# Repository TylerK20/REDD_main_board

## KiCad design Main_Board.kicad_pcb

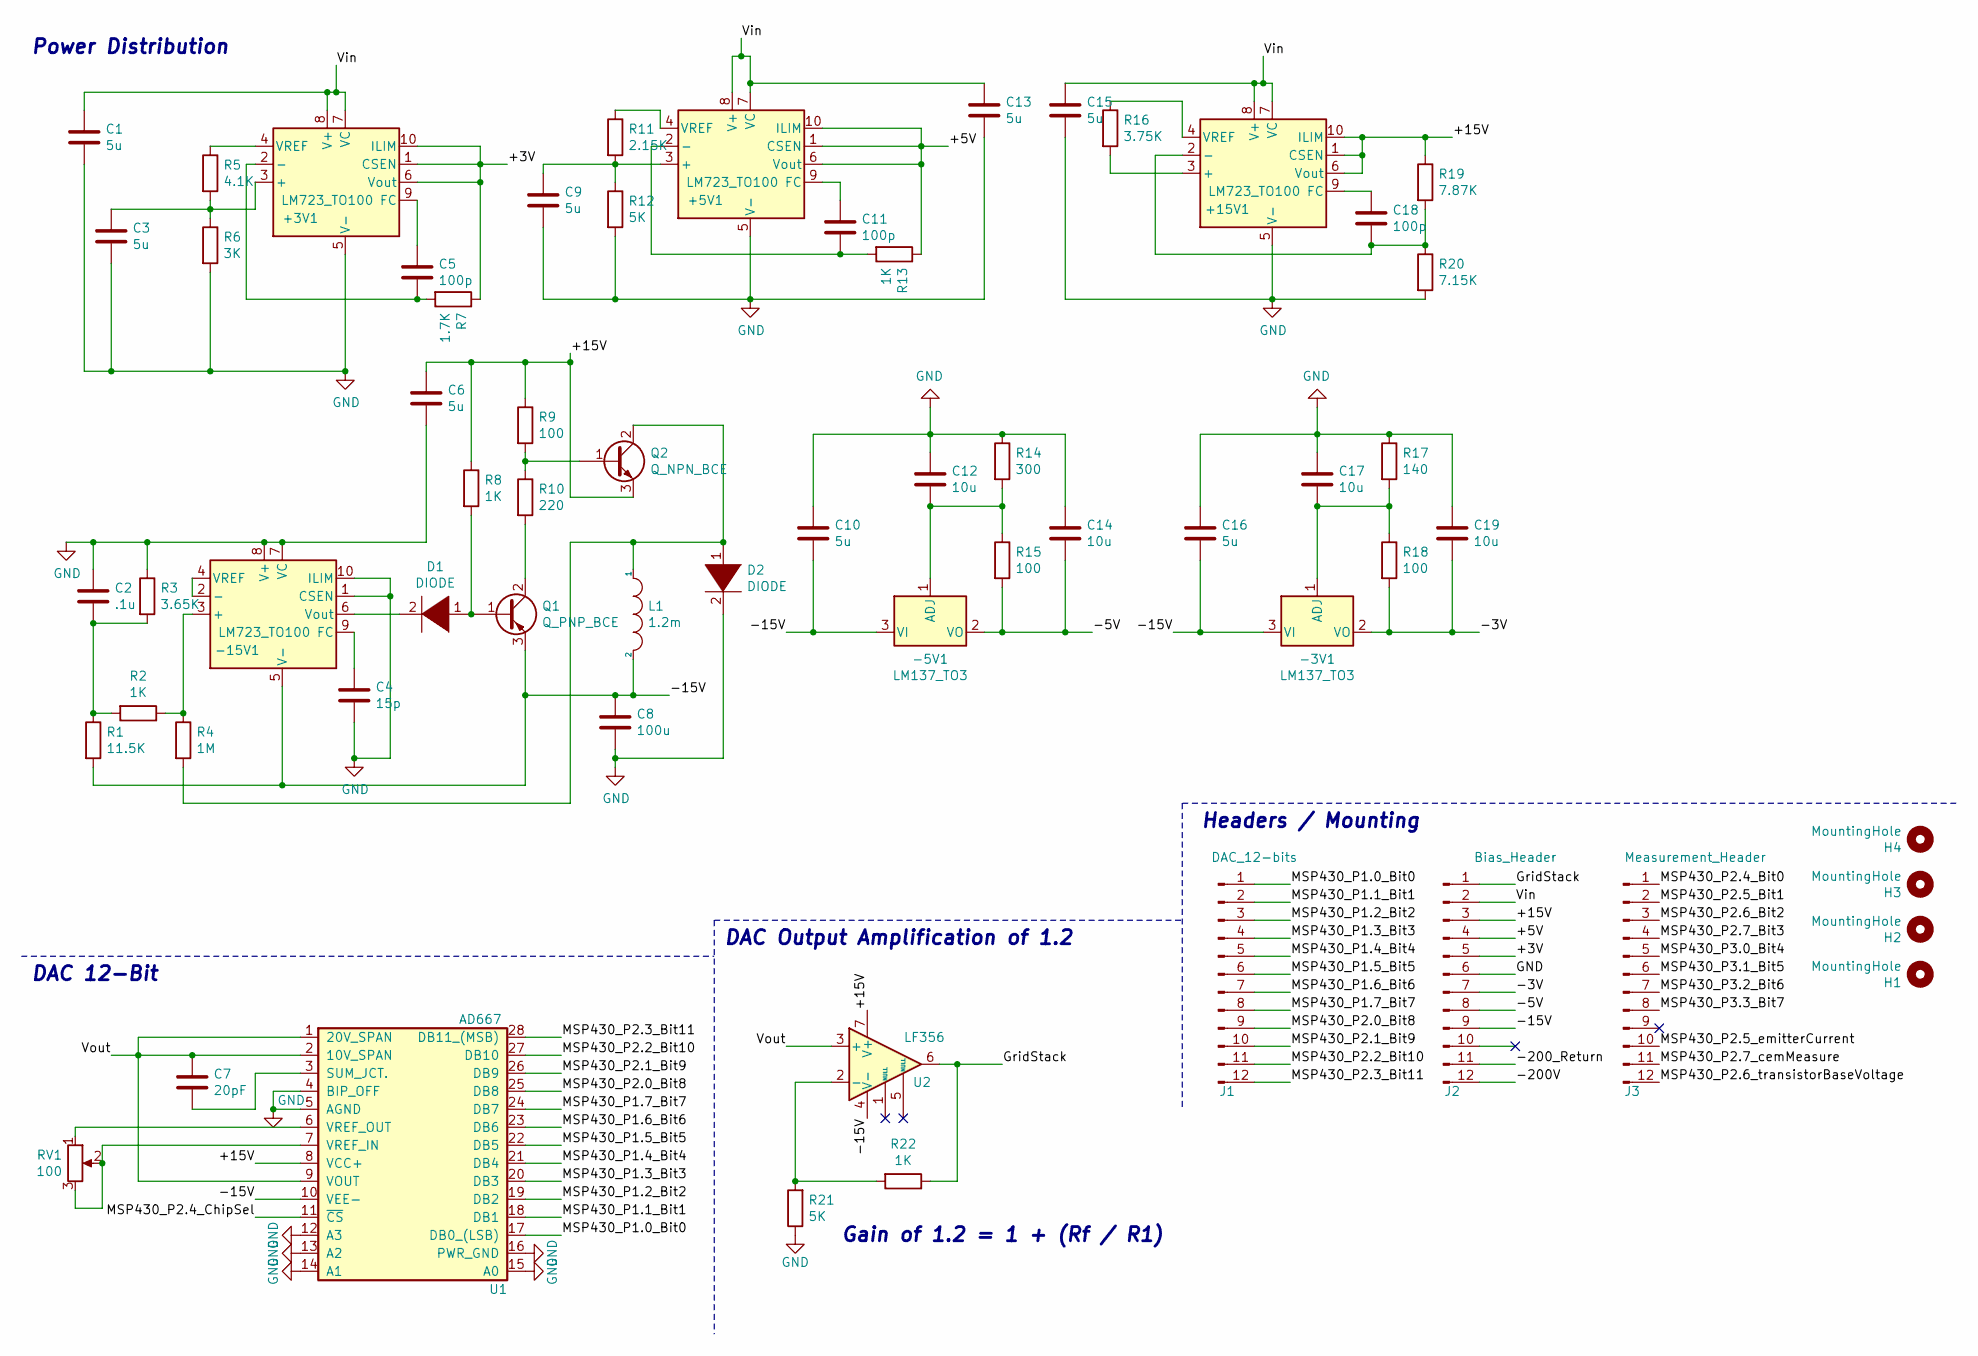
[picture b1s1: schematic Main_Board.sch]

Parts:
+3V1, +5V1, +15V1: LM723_TO100; TO-100-10
-3V1, -5V1: LM137_TO3; TO-39-3
-15V1: LM723_TO100; TO-100-10
C1, C3, C6, C9, C10, C13, C15, C16: 5u; C_0805_2012Metric
C2: .1u; C_0805_2012Metric
C4: 15p; C_0805_2012Metric
C5, C11, C18: 100p; C_0805_2012Metric
C7: 20pF; C_0805_2012Metric
C8: 100u; C_0805_2012Metric
C12, C14, C17, C19: 10u; C_0805_2012Metric
D1: DIODE; D_SMA
D2: DIODE; D_SMC
H1, H2, H3, H4: MountingHole; MountingHole_3.5mm
J1: DAC_12-bits; PinHeader_1x12_P2.54mm_Vertical
J2: Bias_Header; PinHeader_1x12_P2.54mm_Vertical
J3: Measurement_Header; PinHeader_1x12_P2.54mm_Vertical
L1: 1.2m; L_0805_2012Metric
Q1: Q_PNP_BCE; SOT-23
Q2: Q_NPN_BCE; SOT-223
R1: 11.5K; R_0805_2012Metric
R2, R8, R13, R22: 1K; R_0805_2012Metric
R3: 3.65K; R_0805_2012Metric
R4: 1M; R_0805_2012Metric
R5: 4.1K; R_0805_2012Metric
R6: 3K; R_0805_2012Metric
R7: 1.7K; R_0805_2012Metric
R9, R15, R18: 100; R_0805_2012Metric
R10: 220; R_0805_2012Metric
R11: 2.15K; R_0805_2012Metric
R12, R21: 5K; R_0805_2012Metric
R14: 300; R_0805_2012Metric
R16: 3.75K; R_0805_2012Metric
R17: 140; R_0805_2012Metric
R19: 7.87K; R_0805_2012Metric
R20: 7.15K; R_0805_2012Metric
RV1: 100; Potentiometer_Bourns_3299W_Vertical
U1: AD667; AD667_12-bit_DAC
U2: LF356; DIP-8_W7.62mm

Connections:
/+3V: +3V1.1 (CSEN), +3V1.6 (Vout), +3V1.10 (ILIM), J2.5, R7.1
/+5V: +5V1.1 (CSEN), +5V1.6 (Vout), +5V1.10 (ILIM), J2.4, R13.1
/+15V: +15V1.1 (CSEN), +15V1.6 (Vout), +15V1.10 (ILIM), C6.1, J2.3, Q2.3 (E), R8.1, R9.1, R19.1, U1.8 (VCC+), U2.7 (V+)
/-3V: -3V1.2 (VO), C19.2, J2.7, R18.2
/-5V: -5V1.2 (VO), C14.2, J2.8, R15.2
/-15V: -3V1.3 (VI), -5V1.3 (VI), -15V1.5 (V-), C8.1, C10.2, C16.2, J2.9, L1.2, Q1.3 (E), R1.2, U1.10 (VEE-), U2.4 (V-)
/-200V: J2.12
/-200_Return: J2.11
/GridStack: J2.1, R22.1, U2.6
/MSP430_P1.0_Bit0: J1.1, U1.17 (DB0_(LSB))
/MSP430_P1.1_Bit1: J1.2, U1.18 (DB1)
/MSP430_P1.2_Bit2: J1.3, U1.19 (DB2)
/MSP430_P1.3_Bit3: J1.4, U1.20 (DB3)
/MSP430_P1.4_Bit4: J1.5, U1.21 (DB4)
/MSP430_P1.5_Bit5: J1.6, U1.22 (DB5)
/MSP430_P1.6_Bit6: J1.7, U1.23 (DB6)
/MSP430_P1.7_Bit7: J1.8, U1.24 (DB7)
/MSP430_P2.0_Bit8: J1.9, U1.25 (DB8)
/MSP430_P2.1_Bit9: J1.10, U1.26 (DB9)
/MSP430_P2.2_Bit10: J1.11, U1.27 (DB10)
/MSP430_P2.3_Bit11: J1.12, U1.28 (DB11_(MSB))
/MSP430_P2.4_Bit0: J3.1
/MSP430_P2.4_ChipSel: U1.11 (~CS)
/MSP430_P2.5_Bit1: J3.2
/MSP430_P2.5_emitterCurrent: J3.10
/MSP430_P2.6_Bit2: J3.3
/MSP430_P2.6_transistorBaseVoltage: J3.12
/MSP430_P2.7_Bit3: J3.4
/MSP430_P2.7_cemMeasure: J3.11
/MSP430_P3.0_Bit4: J3.5
/MSP430_P3.1_Bit5: J3.6
/MSP430_P3.2_Bit6: J3.7
/MSP430_P3.3_Bit7: J3.8
/Vin: +3V1.7 (VC), +3V1.8 (V+), +5V1.7 (VC), +5V1.8 (V+), +15V1.7 (VC), +15V1.8 (V+), C1.1, C13.1, C15.1, J2.2
/Vout: C7.1, U1.1 (20V_SPAN), U1.2 (10V_SPAN), U1.9 (VOUT), U2.3 (+)
GND: +3V1.5 (V-), +5V1.5 (V-), +15V1.5 (V-), -15V1.1 (CSEN), -15V1.7 (VC), -15V1.8 (V+), -15V1.10 (ILIM), C1.2, C2.1, C3.2, C4.2, C6.2, C8.2, C9.2, C10.1, C12.1, C13.2, C14.1, C15.2, C16.1, C17.1, C19.1, D2.2 (A), J2.6, R3.1, R6.2, R12.2, R14.1, R17.1, R20.2, R21.1, U1.4 (BIP_OFF), U1.5 (AGND), U1.12 (A3), U1.13 (A2), U1.14 (A1), U1.15 (A0), U1.16 (PWR_GND)
unnamed: +3V1.2 (-), C5.2, R7.2
unnamed: +3V1.3 (+), C3.1, R5.2, R6.1
unnamed: +3V1.4 (VREF), R5.1
unnamed: +3V1.9 (FC), C5.1
unnamed: +5V1.2 (-), C11.2, R13.2
unnamed: +5V1.3 (+), C9.1, R11.2, R12.1
unnamed: +5V1.4 (VREF), R11.1
unnamed: +5V1.9 (FC), C11.1
unnamed: +15V1.2 (-), C18.2, R19.2, R20.1
unnamed: +15V1.3 (+), R16.2
unnamed: +15V1.4 (VREF), R16.1
unnamed: +15V1.9 (FC), C18.1
unnamed: -3V1.1 (ADJ), C17.2, R17.2, R18.1
unnamed: -5V1.1 (ADJ), C12.2, R14.2, R15.1
unnamed: -15V1.2 (-), -15V1.4 (VREF)
unnamed: -15V1.3 (+), R2.1, R4.1
unnamed: -15V1.6 (Vout), D1.2 (A)
unnamed: -15V1.9 (FC), C4.1
unnamed: C2.2, R1.1, R2.2, R3.2
unnamed: C7.2, U1.3 (SUM_JCT.)
unnamed: D1.1 (K), Q1.1 (B), R8.2
unnamed: D2.1 (K), L1.1, Q2.2 (C), R4.2
unnamed: Q1.2 (C), R10.2
unnamed: Q2.1 (B), R9.2, R10.1
unnamed: R21.2, R22.2, U2.2 (-)
unnamed: RV1.1, U1.6 (VREF_OUT)
unnamed: RV1.2, RV1.3, U1.7 (VREF_IN)

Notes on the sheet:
Headers / Mounting
DAC 12-Bit
Power Distribution
Gain of 1.2 = 1 + (Rf / R1)
DAC Output Amplification of 1.2

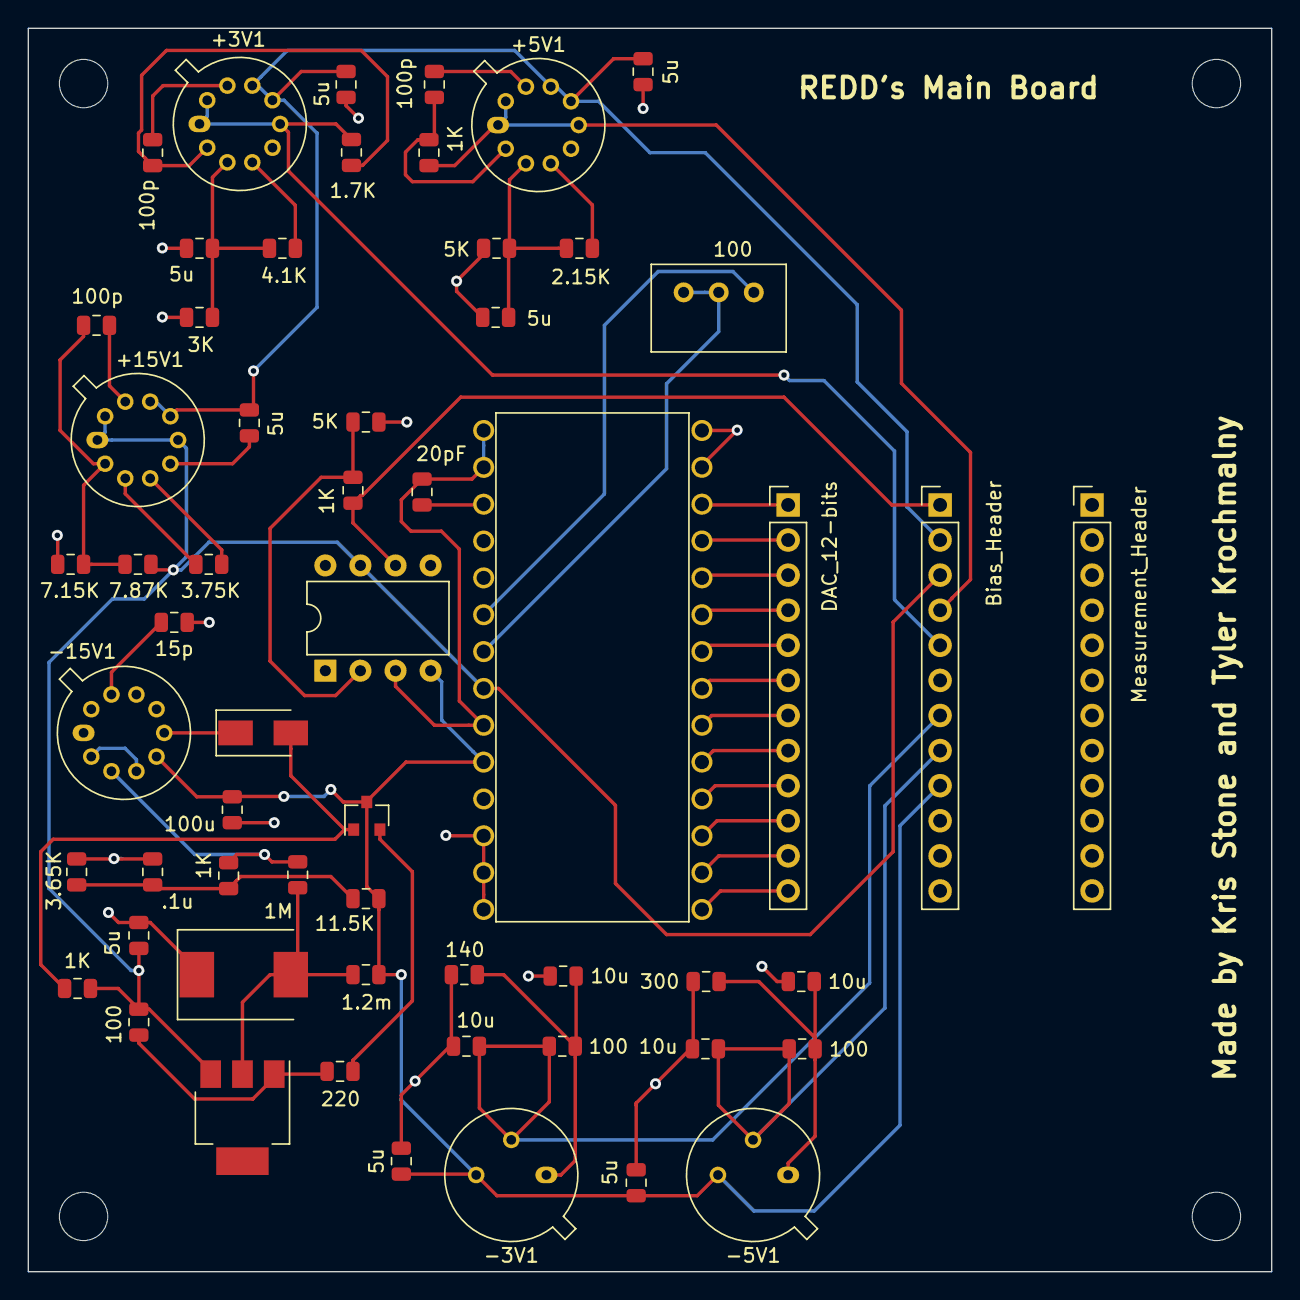
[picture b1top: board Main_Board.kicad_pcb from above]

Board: 2 copper layers, 90.0 x 90.0 mm, 62 parts (0 on the bottom side), 49 nets.

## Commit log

2019-11-20 README
2019-11-20 Hopefully KiCAD files
2020-01-28 Test
2020-01-29 Removed TEST.txt file and DAC project folder
2020-01-29 Removed TEST.txt and DAC Kicad project folder
2020-01-29 Modified Main_Board.sch to include new REDD_main_board library addition for AD667_12-bit_DAC footprint
2020-01-30 Updated REDD_main_board schematicto include new female pin header connector and verified voltage regulators electrically.
2020-01-30 Minor change
2020-02-11 Added board stacker
2020-02-11 Connections
2020-02-11 Caps
2020-02-13 Pin headers
2020-02-13 diode
2020-02-13 transistors
2020-02-13 Started layout
2020-02-13 keepin on that layout
2020-02-13 grid
2020-02-14 Created both footprint and symbol for DAC AD667, still need to do the layout.
2020-02-14 Layout
2020-02-14 O boi that's a lot of nets
2020-02-14 Pin dimensions
2020-02-14 Outline
2020-02-14 Trying autorouting
2020-02-14 Didn't work
2020-02-14 Start routing
2020-02-14 Finished main traces
2020-02-14 Everything but ground
2020-02-18 Traces
2020-02-18 Grounddddddddddddd
2020-02-18 final ground
2020-02-18 Added the 4 pinheaders
2020-02-19 Holes!
2020-02-19 Hole
2020-02-20 Assigned all pins to MSP430, started layout. Will route traces next. Need to know where the signals are going for the CEM before we can finalze. Will need to adjust everything around on the layout to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
2020-02-20 updated routing for DAC and op-amp. Added mounting holes and moved Tyler's traces around. PLEASE CHECK FOR ACCURACY.
2020-02-20 Traces Boi
2020-02-20 All traced
2020-02-20 Final
2020-02-21 Moved holes
2020-02-21 Final Changes
2020-02-22 Needed to update sizing of DAC pin holes to 1.02mm, caught my initial error.
2020-02-22 Shortened to 9cm
2020-02-22 Mounting holes
2020-02-22 Ground Plane
2020-02-22 getting rid of ground
2020-02-22 Re-tracing
2020-02-22 Everything but gnd
2020-02-22 Done
2020-02-22 Added DAC
2020-02-22 Stuff
2020-02-22 Added 8bit DAC
2020-02-26 Defined and added 8-bit DAC for CEM transistor base voltage control to schematic and layout. Still need to do the routing, waiting on clarification of analog output voltage range of 0-2.56V or 0-10V 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
2020-02-28 Finished schematic and layout of 8-bit DAC for CEM transistor control. Adding GND plane to bottom copper.
2020-02-29 Update Schematic
2020-02-29 Added another 12-pin
2020-02-29 Re-routing
2020-02-29 Pins
2020-02-29 Got rid of 8-bit DAC
2020-02-29 GND plane
2020-03-03 Update fp-info-cache
2020-03-03 Changing values to silk screen
2020-03-03 Did it?
2020-03-03 Added names
2020-03-04 Gerbers
2020-03-04 Zipped
2020-03-04 fuck da back silkscreen
2020-03-04 Gerbs
2020-03-04 All Gerbs all day
2020-03-06 -200 Return
2020-03-17 Added the micro-controller code to this repo so it all lives in one place.
2020-03-17 Added as a test
2020-03-17 deleted test file
2020-03-24 update label
2020-04-17 Cleaned up folder a bit
2020-04-17 Added paste
